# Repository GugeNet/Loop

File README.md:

# Loop
4-track Eurorack Looper

A 4 hp wide 3U Eurorack module designed to be as simple as possible, but not simpler.

The user interface is limited but based on an idea of creating a linguistic model.

Not all of the ideas are implemented yet.

The commands consists of verbs: record, clear and loop. There are buttons for record and clear, a trigger input for loop.
In most situations there is also an implicit verb, such as mute.
The time aspect in the commands are either immidiate or suspended until loop. A short press means now, a long press means after the next loop command.
The objects are the four tracks.
The module will ask the user to select track by blinking the four track-buttons, or simetimes only the applicable tracks if appropriate.

Examples:

While playing click a green button and the track is muted and the button goues off.
Press the button for half a second instead of cust clicking and the button will blink green and start playing after the next loop.

Hold down record and notice all tracks blinking red as the module wants to know where to record. You can press one or more tracks and they will record after loop.

Another foundational idea is that every button has a function in any situation. There is no illegal action and the module is never unresponsive. The user is boss and presumably always has some intention.

So if the button for a blank track is pressed, it is presumed that record is the correct operation, while play is implicit for a track with sound.

The connections are stereo inputs and stereo outputs and a trigger input for loop.

There are six buttons. One bi-color illuminated pushbutton for each of the four tracks, one for clearing and one for record.

The basic operation of the module is to record to or play from four sound buffers and then on trigger loop to the beginning.

The module will always pass incoming sound through. Recording is additive, that is to say it doesn't remove existing sound from the track before recording.
Recording takes just the incoming sound.

Playing also adds sound to the incoming sound and when several tracks are playing they are all added equally to the incoming sound.

On reception of the loop trig the following scenarios are performed:

Playing -> Playing
Recording -> Playing
Muted -> Muted

The user can cue playing, recording or muting to happen on loop.

Record -> Track (long)
Track (long)
Clear -> Track (long)

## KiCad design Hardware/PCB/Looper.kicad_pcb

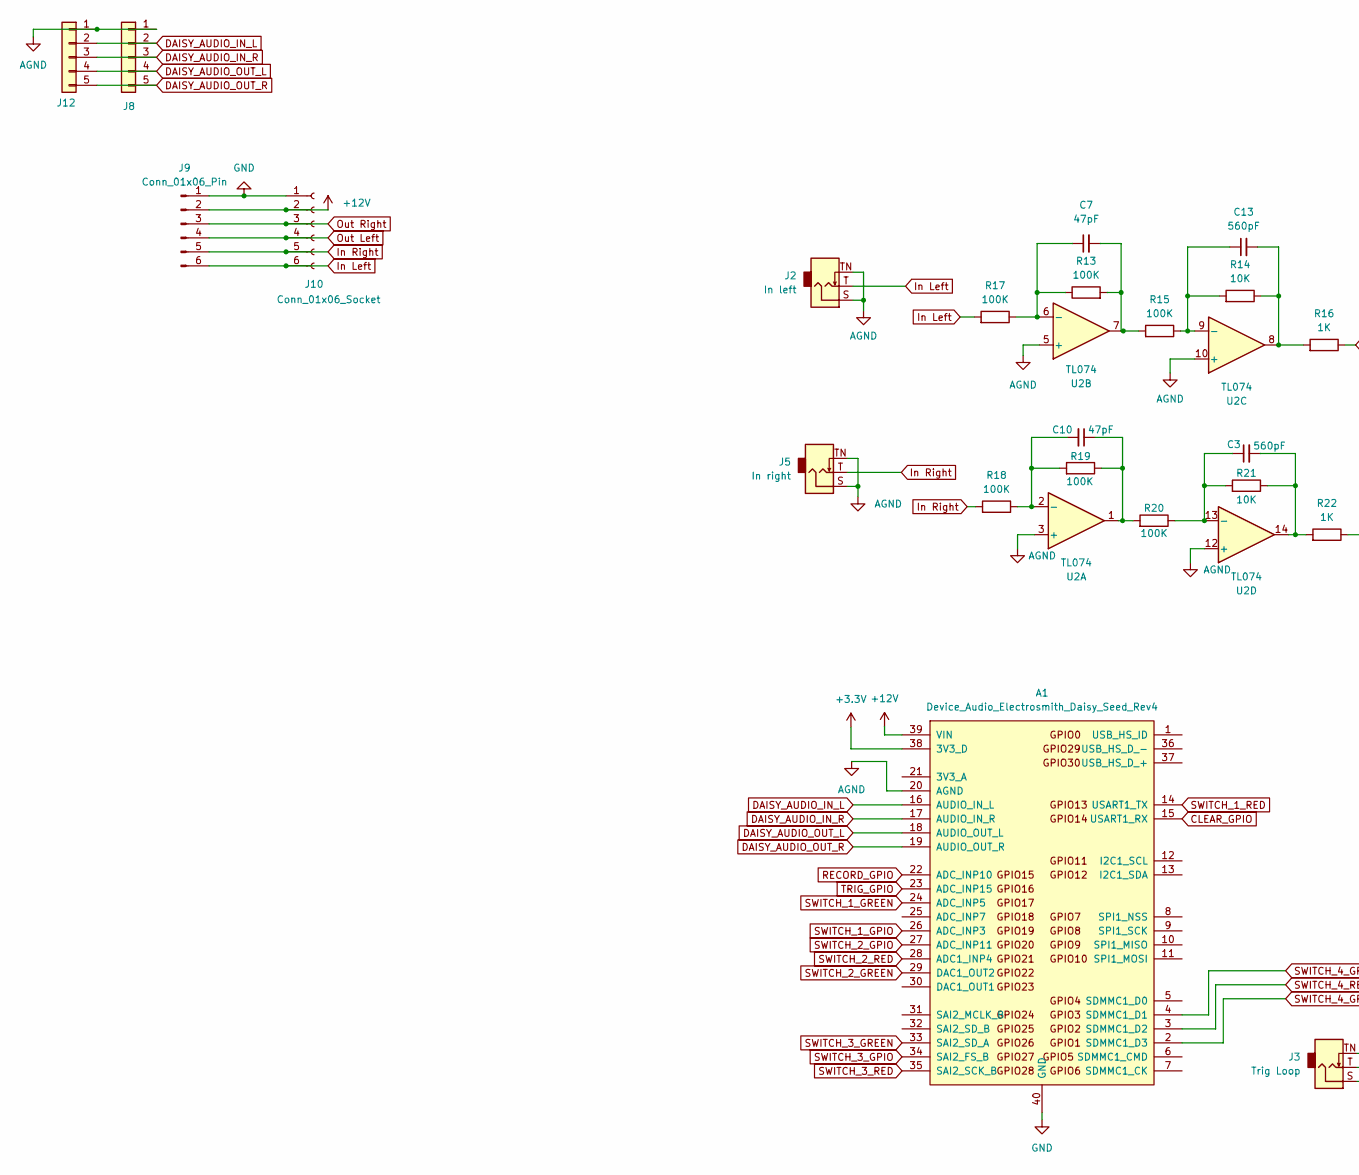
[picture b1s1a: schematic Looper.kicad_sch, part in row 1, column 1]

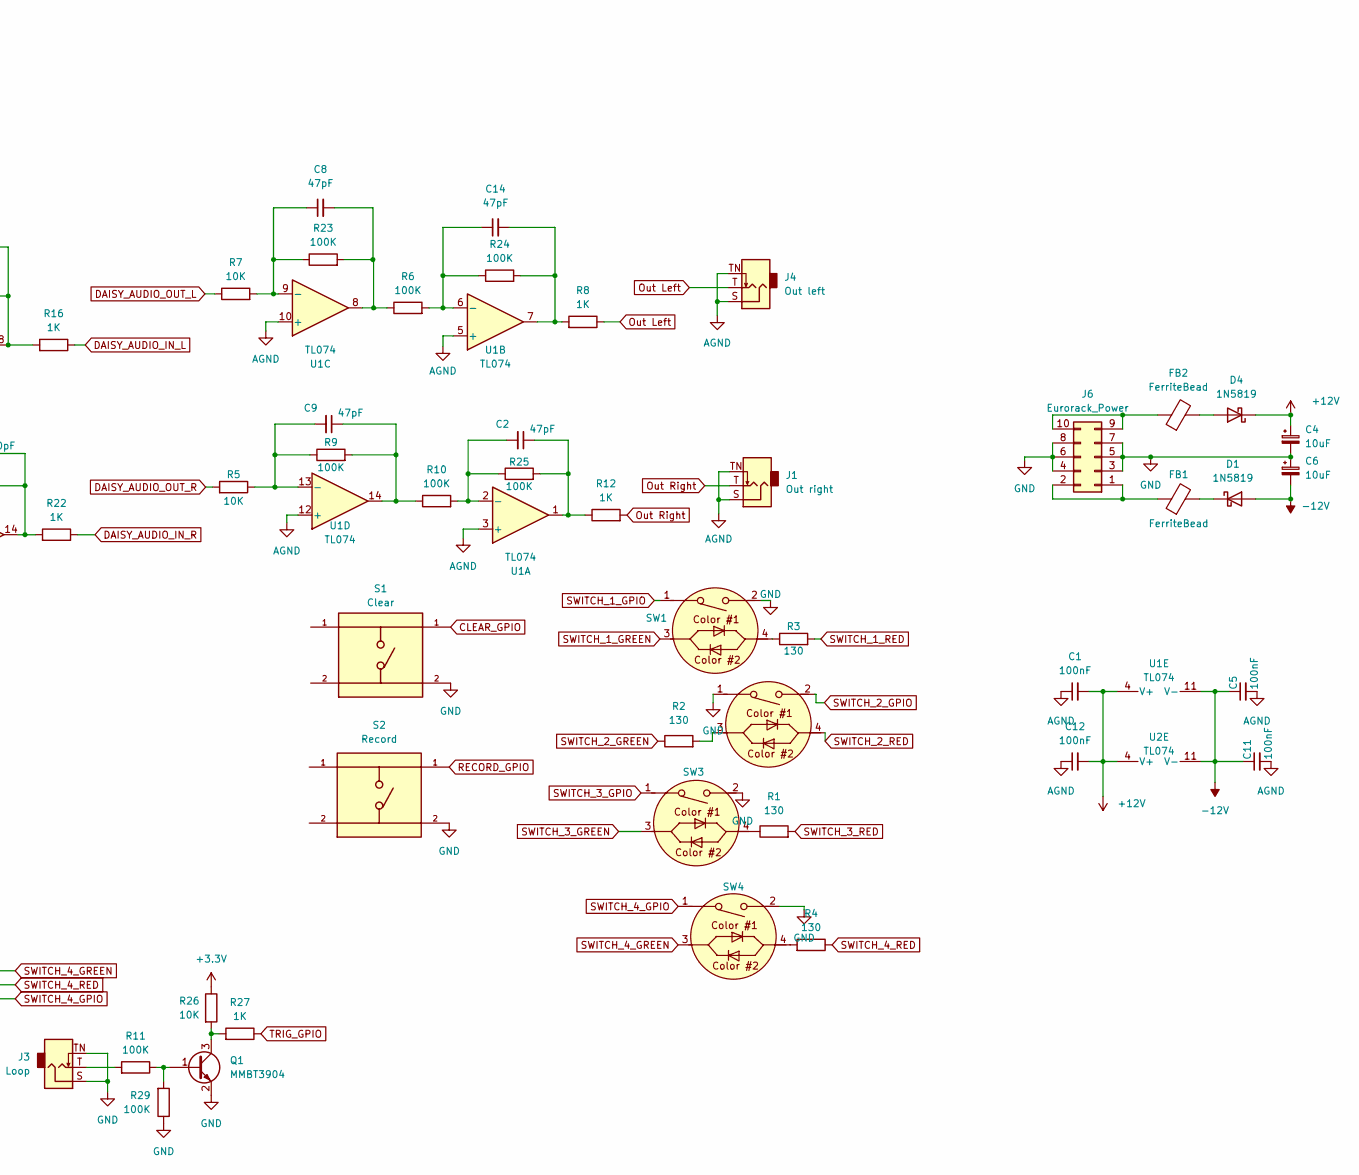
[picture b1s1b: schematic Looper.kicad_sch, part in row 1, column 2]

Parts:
A1: Device_Audio_Electrosmith_Daisy_Seed_Rev4; Device_Audio_Electrosmith_Daisy_Seed
C1, C5, C11, C12: 100nF; C_0603_1608Metric; LCSC C14663
C2, C7, C8, C9, C10, C14: 47pF; C_0603_1608Metric; LCSC C1671
C3, C13: 560pF; C_0603_1608Metric; LCSC C458906
C4, C6: 10uF; CP_Elec_4x5.4; LCSC C88654
D1, D4: 1N5819; D_SOD-123; LCSC C5451628
FB1, FB2: FerriteBead; R_0603_1608Metric; LCSC C1002
J1: Out right; Jack_3.5mm_QingPu_WQP-PJ398SM_Vertical
J2: In left; Jack_3.5mm_QingPu_WQP-PJ398SM_Vertical
J3: Trig Loop; Jack_3.5mm_QingPu_WQP-PJ398SM_Vertical
J4: Out left; Jack_3.5mm_QingPu_WQP-PJ398SM_Vertical
J5: In right; Jack_3.5mm_QingPu_WQP-PJ398SM_Vertical
J6: Eurorack_Power; PinHeader_2x05_P2.54mm_Vertical
J8, J12: Conn_01x05; PinHeader_1x05_P2.54mm_Vertical
J9: Conn_01x06_Pin; PinHeader_1x06_P2.54mm_Vertical
J10: Conn_01x06_Socket; PinHeader_1x06_P2.54mm_Vertical
Q1: MMBT3904; SOT-23; LCSC C20526
R1, R2, R3, R4: 130; R_0603_1608Metric; LCSC C22796
R5, R7, R14, R21, R26: 10K; R_0603_1608Metric; LCSC C25804
R6, R9, R10, R11, R13, R15, R17, R18, R19, R20, R23, R24, R25, R29: 100K; R_0603_1608Metric; LCSC C25803
R8, R12, R16, R22, R27: 1K; R_0603_1608Metric; LCSC C21190
S1: Clear; SW_TS02-66-140-BK-160-LCR-D; PARTREV 1.0
S2: Record; SW_TS02-66-140-BK-160-LCR-D; PARTREV 1.0
SW1, SW2, SW3, SW4: D6RLRDGNF1LFS
U1, U2: TL074; SOIC127P600X175-14N; LCSC C12594

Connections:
+3.3V: A1.38 (3V3_D), R26.1
+12V: A1.39 (VIN), C1.2, C4.1, C12.2, D4.1 (K), J9.2, J10.2, U1.4 (V+), U2.4 (V+)
-12V: C5.1, C6.2, C11.1, D1.2 (A), U1.11 (V-), U2.11 (V-)
AGND: A1.20 (AGND), C1.1, C5.2, C11.2, C12.1, J1.S, J1.TN, J2.S, J2.TN, J4.S, J4.TN, J5.S, J5.TN, J8.1, J12.1, U1.3 (+), U1.5 (+), U1.10 (+), U1.12 (+), U2.3 (+), U2.5 (+), U2.10 (+), U2.12 (+)
CLEAR_GPIO: A1.15 (USART1_RX), S1.1
DAISY_AUDIO_IN_L: A1.16 (AUDIO_IN_L), J8.2, J12.2, R16.1
DAISY_AUDIO_IN_R: A1.17 (AUDIO_IN_R), J8.3, J12.3, R22.1
DAISY_AUDIO_OUT_L: A1.18 (AUDIO_OUT_L), J8.4, J12.4, R7.1
DAISY_AUDIO_OUT_R: A1.19 (AUDIO_OUT_R), J8.5, J12.5, R5.2
GND: A1.40 (GND), C4.2, C6.1, J3.S, J3.TN, J6.3, J6.4, J6.5, J6.6, J6.7, J6.8, J9.1, J10.1, Q1.2 (E), R29.1, S1.2, S2.2, SW1.2, SW2.1, SW3.2, SW4.2
In Left: J2.T, J9.6, J10.6, R17.2
In Right: J5.T, J9.5, J10.5, R18.2
unnamed: C2.1, R12.1, R25.2, U1.1
unnamed: C3.2, R21.1, R22.2, U2.14
unnamed: C7.2, R13.2, R15.2, U2.7
unnamed: C8.2, R6.1, R23.2, U1.8
unnamed: C9.1, R9.2, R10.1, U1.14
unnamed: C10.1, R19.1, R20.2, U2.1
unnamed: C13.2, R14.1, R16.2, U2.8
unnamed: C14.2, R8.2, R24.2, U1.7
unnamed: D1.1 (K), FB1.2
unnamed: D4.2 (A), FB2.2
unnamed: J3.T, R11.2
unnamed: FB1.1, J6.1, J6.2
unnamed: FB2.1, J6.9, J6.10
unnamed: Q1.1 (B), R11.1, R29.2
unnamed: Q1.3 (C), R26.2, R27.2
unnamed: R1.1, SW3.4
unnamed: R2.2, SW2.3
unnamed: R3.1, SW1.4
unnamed: R4.2, SW4.4
unnamed: C2.2, R10.2, R25.1, U1.2 (-)
unnamed: C14.1, R6.2, R24.1, U1.6 (-)
unnamed: C8.1, R7.2, R23.1, U1.9 (-)
unnamed: C9.2, R5.1, R9.1, U1.13 (-)
unnamed: C10.2, R18.1, R19.2, U2.2 (-)
unnamed: C7.1, R13.1, R17.1, U2.6 (-)
unnamed: C13.1, R14.2, R15.1, U2.9 (-)
unnamed: C3.1, R20.1, R21.2, U2.13 (-)
Out Left: J4.T, J9.4, J10.4, R8.1
Out Right: J1.T, J9.3, J10.3, R12.2
RECORD_GPIO: A1.22 (ADC_INP10), S2.1
SWITCH_1_GPIO: A1.26 (ADC_INP3), SW1.1
SWITCH_1_GREEN: A1.24 (ADC_INP5), SW1.3
SWITCH_1_RED: A1.14 (USART1_TX), R3.2
SWITCH_2_GPIO: A1.27 (ADC_INP11), SW2.2
SWITCH_2_GREEN: A1.29 (DAC1_OUT2), R2.1
SWITCH_2_RED: A1.28 (ADC1_INP4), SW2.4
SWITCH_3_GPIO: A1.34 (SAI2_FS_B), SW3.1
SWITCH_3_GREEN: A1.33 (SAI2_SD_A), SW3.3
SWITCH_3_RED: A1.35 (SAI2_SCK_B), R1.2
SWITCH_4_GPIO: A1.2 (SDMMC1_D3), SW4.1
SWITCH_4_GREEN: A1.4 (SDMMC1_D1), SW4.3
SWITCH_4_RED: A1.3 (SDMMC1_D2), R4.1
TRIG_GPIO: A1.23 (ADC_INP15), R27.1

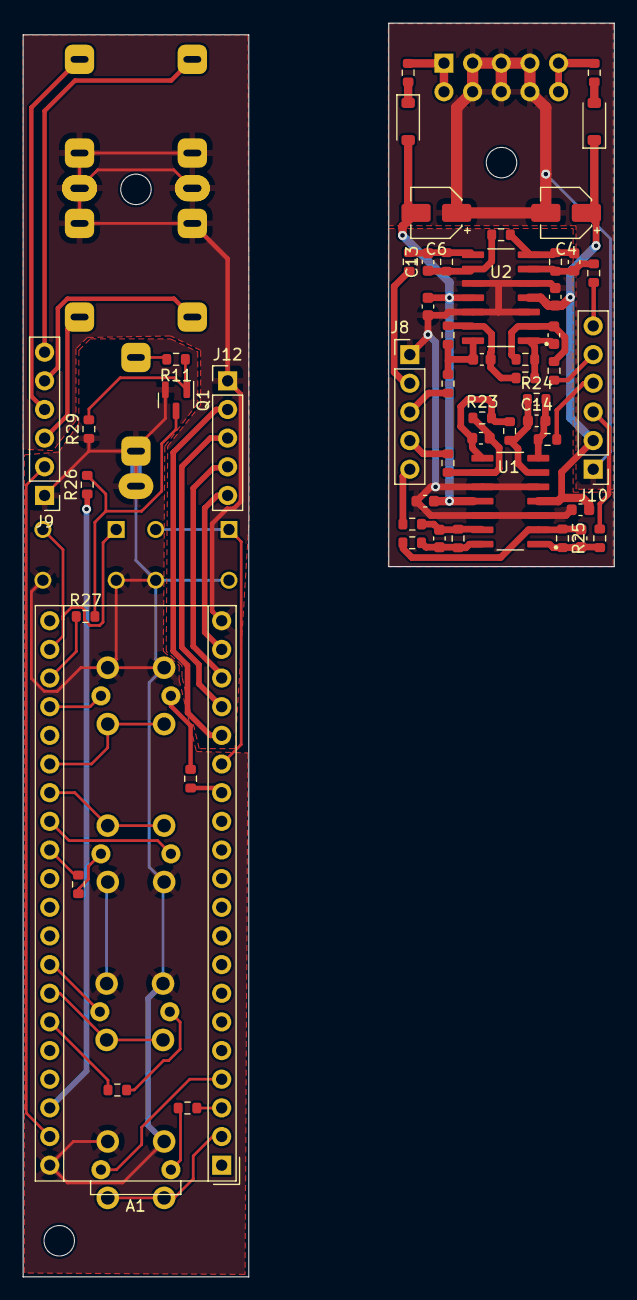
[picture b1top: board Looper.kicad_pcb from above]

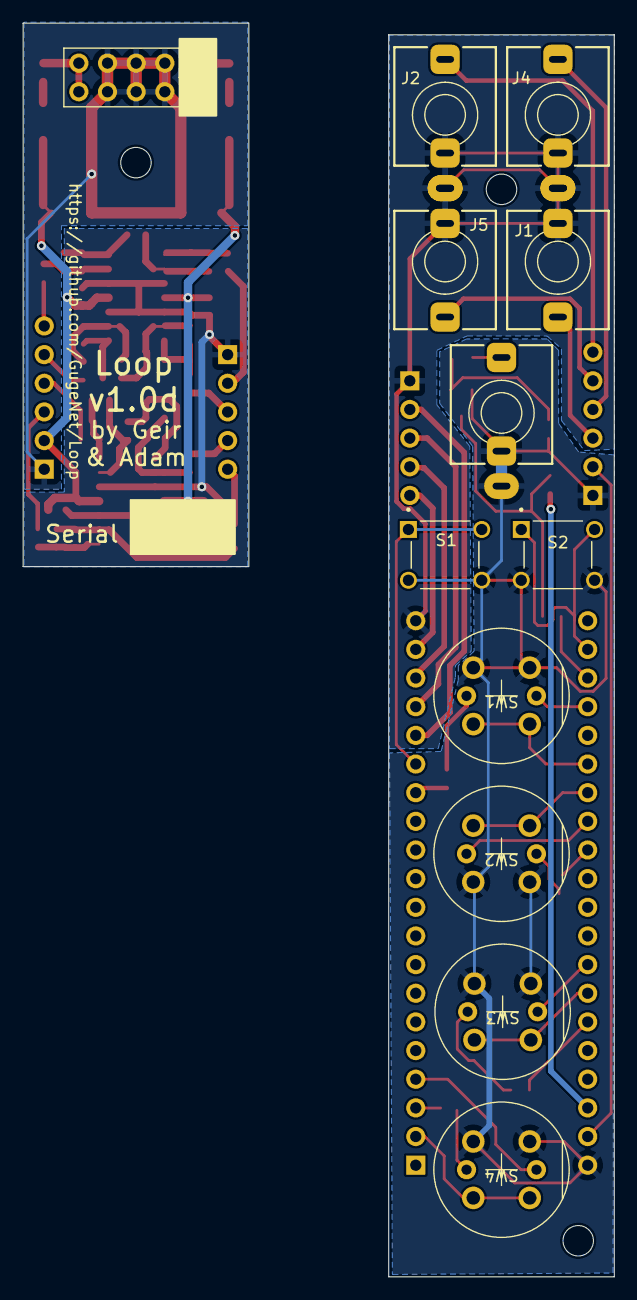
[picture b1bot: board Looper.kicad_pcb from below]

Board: 2 copper layers, 52.4 x 111.1 mm, 69 parts (12 on the bottom side), 55 nets.

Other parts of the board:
MOUNT1, MOUNT1#2, MOUNT1#3: MountingHole_2.7mm_M2.5

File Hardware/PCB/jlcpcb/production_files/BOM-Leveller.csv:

Comment,Designator,Footprint,LCSC,Quantity
FerriteBead,"FB1,FB2",R_0603_1608Metric,C1002,2
TL074,"U1,U2",SOIC127P600X175-14N,C12594,2
100nF,"C1,C11,C12,C5",C_0603_1608Metric,C14663,4
47pF,"C10,C14,C2,C7,C8,C9",C_0603_1608Metric,C1671,6
1K,"R12,R16,R22,R8",R_0603_1608Metric,C21190,4
100K,"R10,R13,R15,R17,R18,R19,R20,R23,R24,R25,R6,R9",R_0603_1608Metric,C25803,12
10K,"R14,R21,R5,R7",R_0603_1608Metric,C25804,4
560pF,"C13,C3",C_0603_1608Metric,C458906,2
1N5819,"D1,D4",D_SOD-123,C5451628,2
10uF,"C4,C6",CP_Elec_4x5.4,C88654,2

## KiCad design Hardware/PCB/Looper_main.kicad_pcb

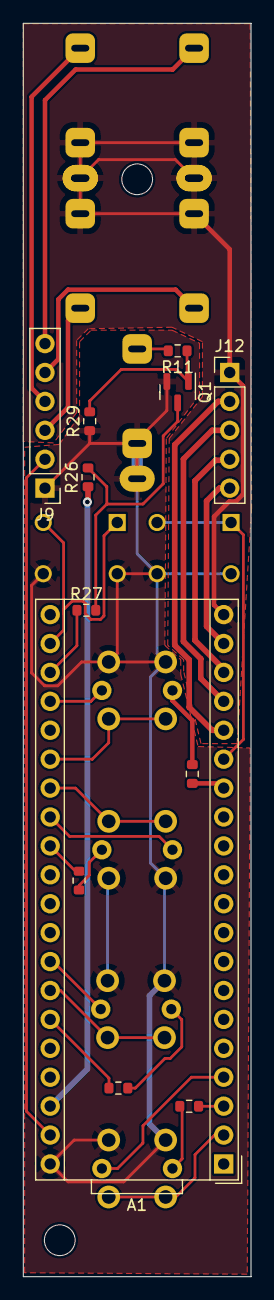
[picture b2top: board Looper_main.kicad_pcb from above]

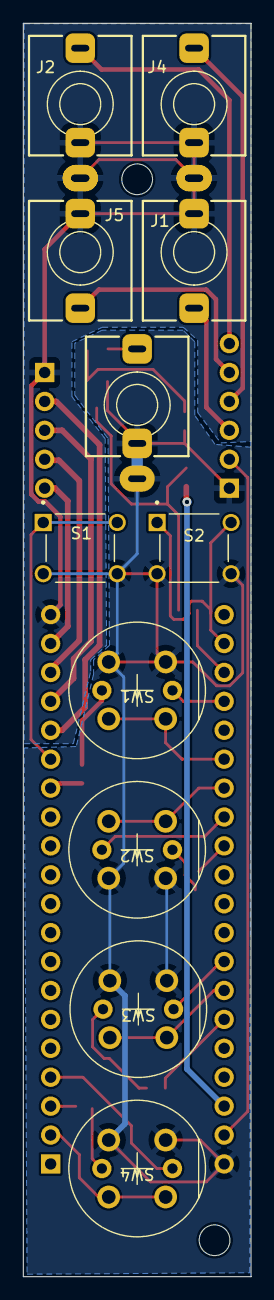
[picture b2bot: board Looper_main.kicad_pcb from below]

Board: 2 copper layers, 20.0 x 110.1 mm, 25 parts (11 on the bottom side), 8 nets.

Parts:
A1: Device_Audio_Electrosmith_Daisy_Seed_Rev4; Device_Audio_Electrosmith_Daisy_Seed
J1: Out right; Jack_3.5mm_QingPu_WQP-PJ398SM_Vertical
J2: In left; Jack_3.5mm_QingPu_WQP-PJ398SM_Vertical
J3: Trig Loop; Jack_3.5mm_QingPu_WQP-PJ398SM_Vertical
J4: Out left; Jack_3.5mm_QingPu_WQP-PJ398SM_Vertical
J5: In right; Jack_3.5mm_QingPu_WQP-PJ398SM_Vertical
J9: Conn_01x06_Pin; PinHeader_1x06_P2.54mm_Vertical
J12: Conn_01x05; PinHeader_1x05_P2.54mm_Vertical
MOUNT1, MOUNT1#2: MountingHole_2.7mm_M2.5
Q1: MMBT3904; SOT-23
R1, R2, R3, R4: 130; R_0603_1608Metric
R11, R29: 100K; R_0603_1608Metric
R26: 10K; R_0603_1608Metric
R27: 1K; R_0603_1608Metric
S1: Clear; SW_TS02-66-140-BK-160-LCR-D
S2: Record; SW_TS02-66-140-BK-160-LCR-D
SW1, SW2, SW3, SW4: D6RLRDGNF1LFS

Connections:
+3.3V: A1.38 (3V3_D), R26.1
+12V: A1.39 (VIN), J9.2
GND: A1.40 (GND), J3.S, J3.TN, J9.1, Q1.2 (E), R29.1, S1.2, S2.2, SW1.2, SW2.1, SW3.2, SW4.2
In Left: J2.T, J9.6
unnamed: R3.1, SW1.4
unnamed: R4.2, SW4.4
Out Left: J4.T, J9.4
Out Right: J1.T, J9.3

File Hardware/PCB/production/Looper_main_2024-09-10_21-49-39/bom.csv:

Designator,Footprint,Quantity,Value,LCSC Part #
J1,Jack_3.5mm_QingPu_WQP-PJ398SM_Vertical,1,Out right,
J2,Jack_3.5mm_QingPu_WQP-PJ398SM_Vertical,1,In left,
J3,Jack_3.5mm_QingPu_WQP-PJ398SM_Vertical,1,Trig Loop,
J4,Jack_3.5mm_QingPu_WQP-PJ398SM_Vertical,1,Out left,
J5,Jack_3.5mm_QingPu_WQP-PJ398SM_Vertical,1,In right,
Q1,SOT-23,1,MMBT3904,C20526
"R1, R2, R3, R4",0603,4,130,
"R11, R29",0603,2,100K,C25803
R26,0603,1,10K,C25804
R27,0603,1,1K,C21190
S1,SW_TS02-66-140-BK-160-LCR-D,1,Clear,
S2,SW_TS02-66-140-BK-160-LCR-D,1,Record,

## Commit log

2023-11-21 Initial test with button and leds
2023-11-22 UI Classes
2023-11-22 Blink
2023-11-24 Track buttons work
2023-11-25 Looping function
2023-11-25 Ignore build
2023-11-25 fixed adverse head promotion
2023-11-25 Recording button working
2023-12-06 Front panel design
2023-12-27 Hardware v.0.9.2
2024-08-15 Track Buttons working
2024-08-20 Hardware added
2024-08-21 Version 1.0 of hardware ordered
2024-08-28 Leveller 1.0b
2024-08-29 Fixed power diode polarity
2024-09-03 Production files
2024-09-03 new intracard connections
2024-09-08 more labels
2024-09-08 Endret hele leveller
2024-09-19 HW 1.0c
2024-11-07 Version 1.0d hardware
2024-11-11 record and clear buttons
2024-11-28 HW Version D
2024-11-29 More functions
2024-12-10 Minor bugfixes
